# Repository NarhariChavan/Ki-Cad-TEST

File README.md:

# Ki-Cad-TEST
This is the Test Repo for My Connection and Setup

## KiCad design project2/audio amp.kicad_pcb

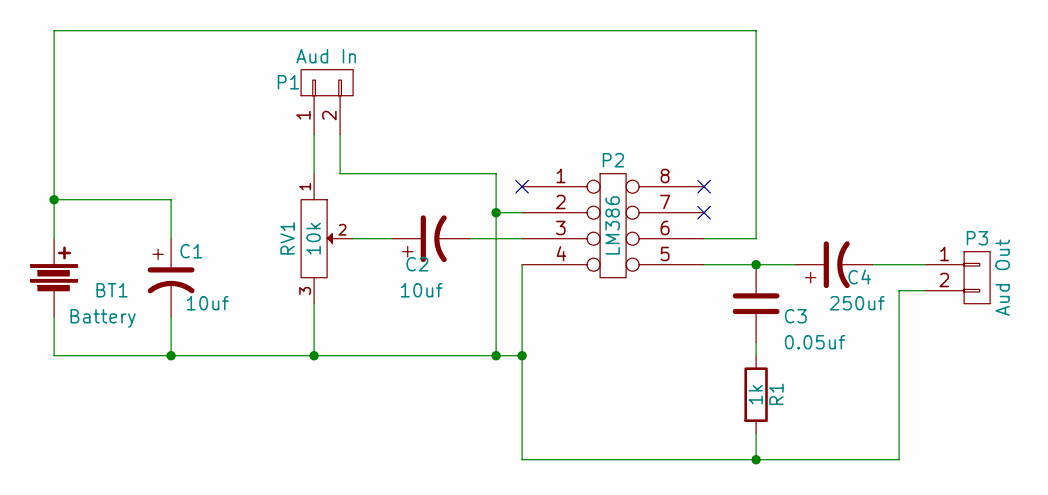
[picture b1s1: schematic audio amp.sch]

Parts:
BT1: Battery; Socket_Strip_Straight_1x02
C1, C2: 10uf; C_Radial_D5_L6_P2.5
C3: 0.05uf; C_Disc_D6_P5
C4: 250uf; C_Radial_D10_L13_P5
P1: Aud In; Socket_Strip_Straight_1x02
P2: LM386; DIP-8_W7.62mm_LongPads
P3: Aud Out; Socket_Strip_Straight_1x02
R1: 1k; Resistor_Horizontal_RM7mm
RV1: 10k; Potentiometer_Trimmer-Suntan-TSR-3386P

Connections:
unnamed: BT1.1, C1.1, P2.6
unnamed: BT1.2, C1.2, P1.2, P2.2, P2.4, P3.2, R1.2, RV1.3
unnamed: C2.1, RV1.2
unnamed: C2.2, P2.3
unnamed: C3.1, C4.1, P2.5
unnamed: C3.2, R1.1
unnamed: C4.2, P3.1
unnamed: P1.1, RV1.1

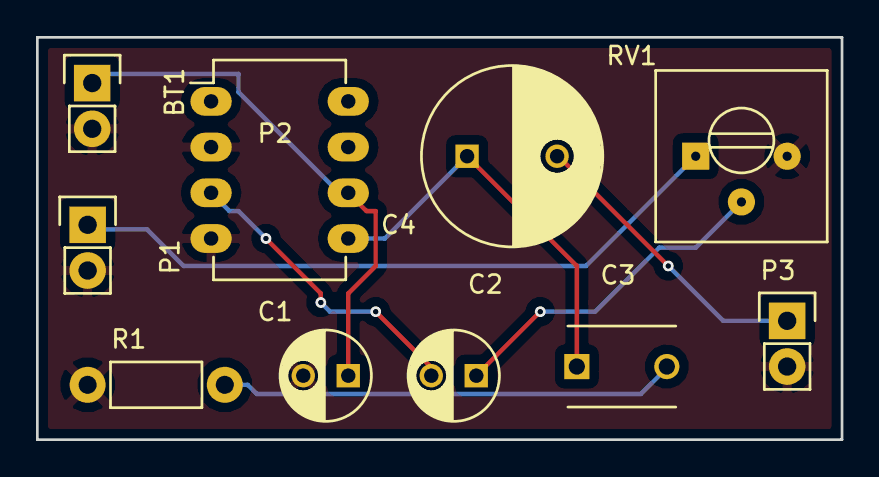
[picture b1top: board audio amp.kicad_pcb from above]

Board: 2 copper layers, 44.7 x 22.4 mm, 10 parts (0 on the bottom side), 8 nets.

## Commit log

2016-09-30 Audio Amplifier
    This is for Clasa F Audio Amplifier
2016-09-30 applied the border to ckt
    border to ckt
